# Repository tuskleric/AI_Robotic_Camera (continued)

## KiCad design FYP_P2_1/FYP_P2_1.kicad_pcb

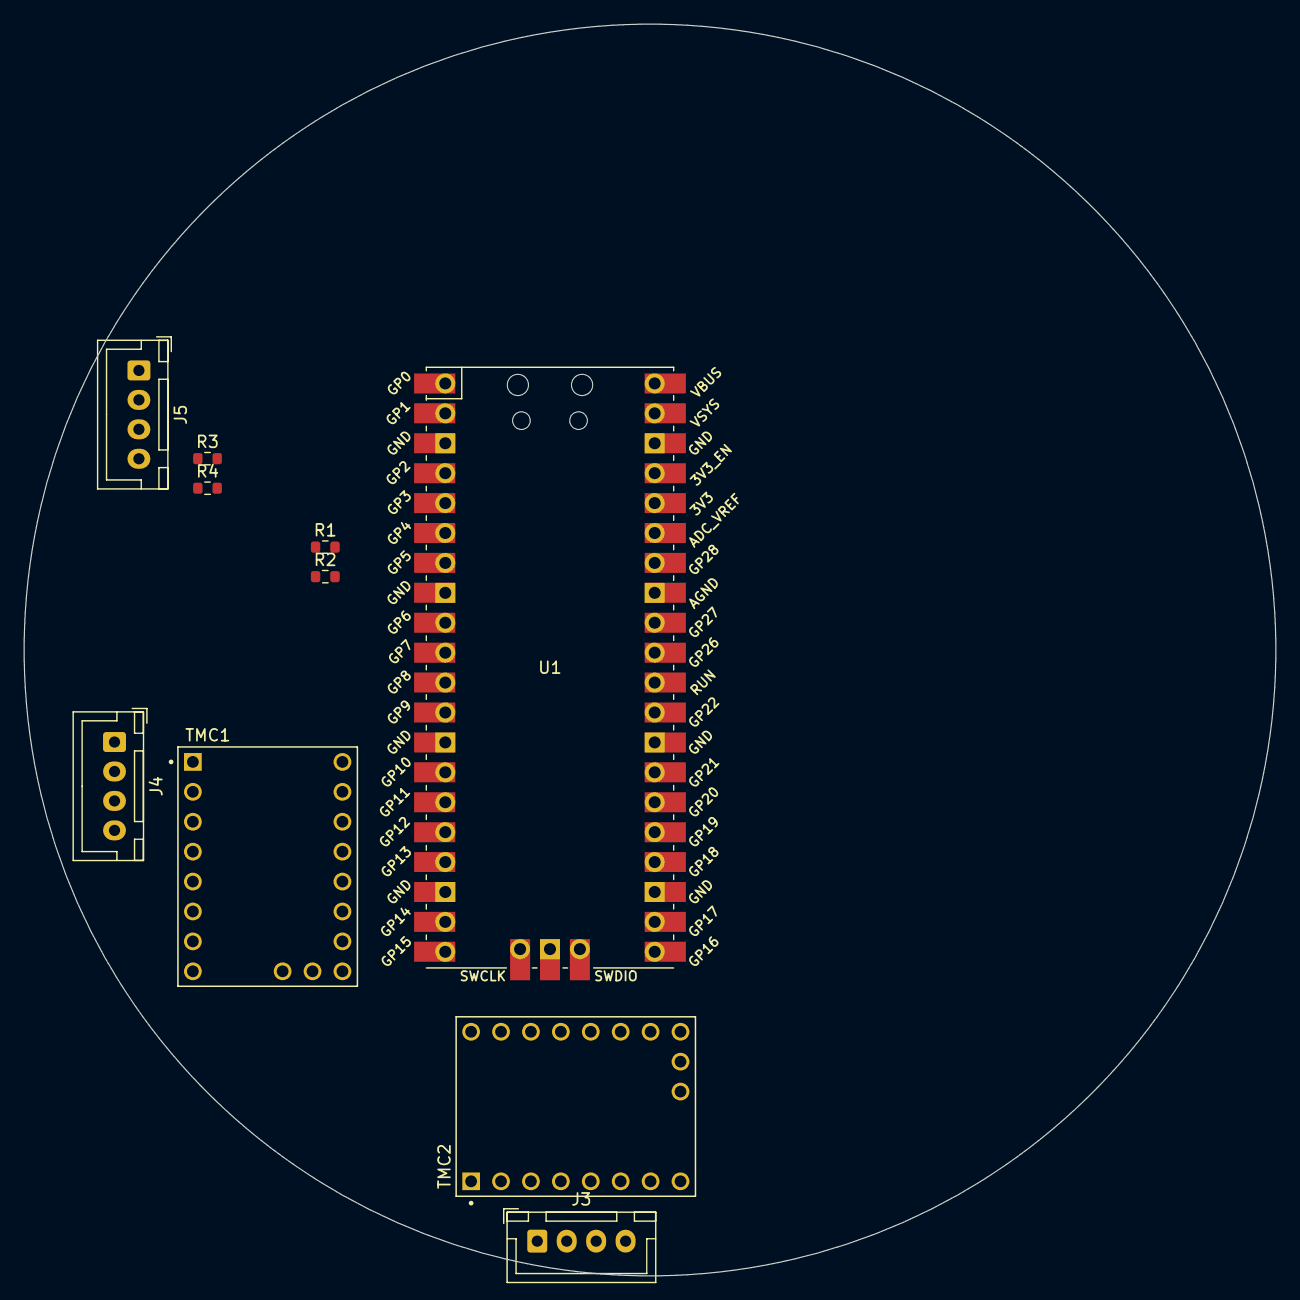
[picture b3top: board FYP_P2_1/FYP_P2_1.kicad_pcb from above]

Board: 4 copper layers, 106.3 x 106.3 mm, 10 parts (0 on the bottom side), 27 nets, no tracks yet.

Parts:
J3, J4, J5: Conn_01x04; JST_XH_B4B-XH-A_1x04_P2.50mm_Vertical
R1, R2: TBD; R_0603_1608Metric
R3, R4: 4k7; R_0603_1608Metric
TMC1, TMC2: MODULE_TMC2209_SILENTSTEPSTICK
U1: Pico; RPi_Pico_SMD_TH

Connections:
+3V3: R1.2, R2.2, R3.2, R4.2
+12V: TMC1.2 (VDD), TMC2.2 (VDD)
/MotorA1A: J4.2, TMC1.4 (1A)
/MotorA1B: J4.1, TMC1.3 (1B)
/MotorA2A: J4.3, TMC1.5 (2A)
/MotorA2B: J4.4, TMC1.6 (2B)
/MotorB1A: J3.2, TMC2.4 (1A)
/MotorB1B: J3.1, TMC2.3 (1B)
/MotorB2A: J3.3, TMC2.5 (2A)
/MotorB2B: J3.4, TMC2.6 (2B)
DIRA: TMC1.8 (DIR), U1.14 (GPIO10)
DIRB: TMC2.8 (DIR), U1.24 (GPIO18)
ENCODER_1A: R1.1, U1.4 (GPIO2)
ENCODER_1B: R2.1, U1.5 (GPIO3)
GND: TMC1.1 (GND), TMC1.7 (GND), TMC2.1 (GND), TMC2.7 (GND), U1.3 (GND), U1.8 (GND), U1.13 (GND), U1.23 (GND), U1.28 (GND), U1.38 (GND), U1.42 (GND)
MS1A: TMC1.14 (MS1), U1.20 (GPIO15)
MS1B: TMC2.14 (MS1), U1.22 (GPIO17)
MS2A: TMC1.13 (MS2), U1.19 (GPIO14)
MS2B: TMC2.13 (MS2), U1.21 (GPIO16)
SCL: J5.4, R4.1, U1.2 (GPIO1)
SDA: J5.3, R3.1, U1.1 (GPIO0)
STEPA: TMC1.9 (STEP), U1.15 (GPIO11)
STEPB: TMC2.9 (STEP), U1.25 (GPIO19)
UART_RX_A: TMC1.12 (UART_RX), U1.17 (GPIO13)
UART_RX_B: TMC2.12 (UART_RX), U1.27 (GPIO21)
UART_TX_A: TMC1.11 (UART_TX), U1.16 (GPIO12)
UART_TX_B: TMC2.11 (UART_TX), U1.26 (GPIO20)

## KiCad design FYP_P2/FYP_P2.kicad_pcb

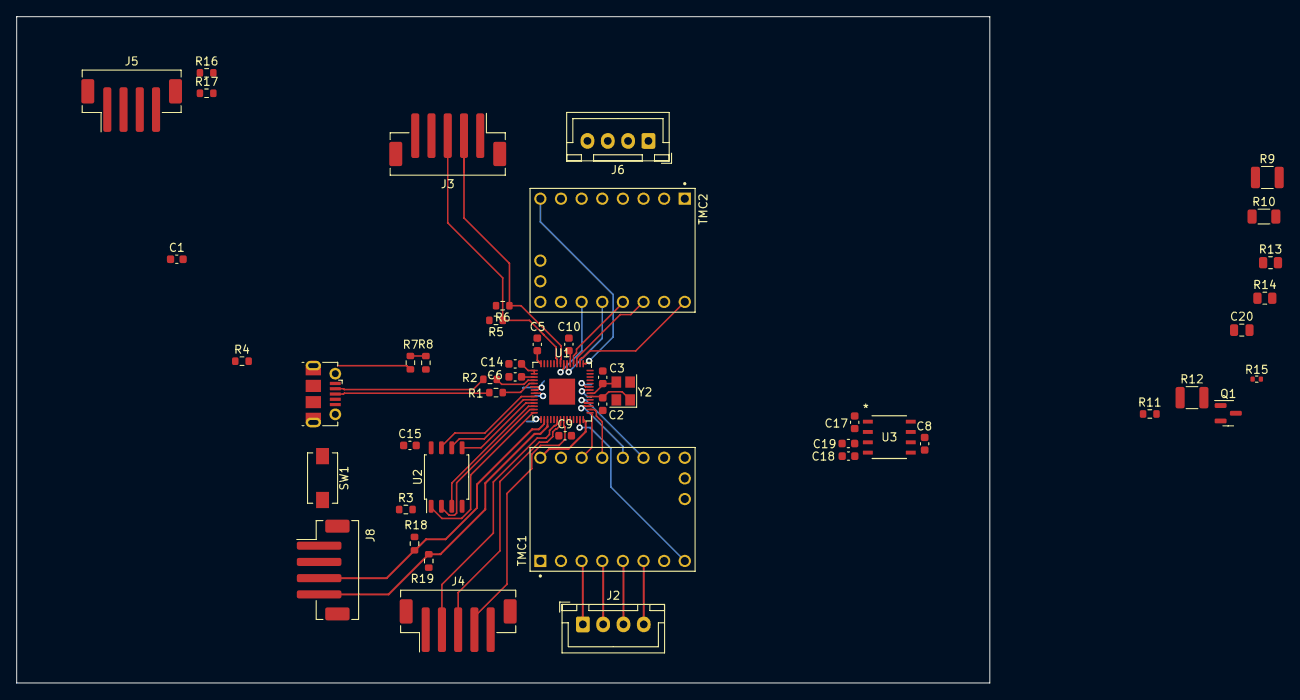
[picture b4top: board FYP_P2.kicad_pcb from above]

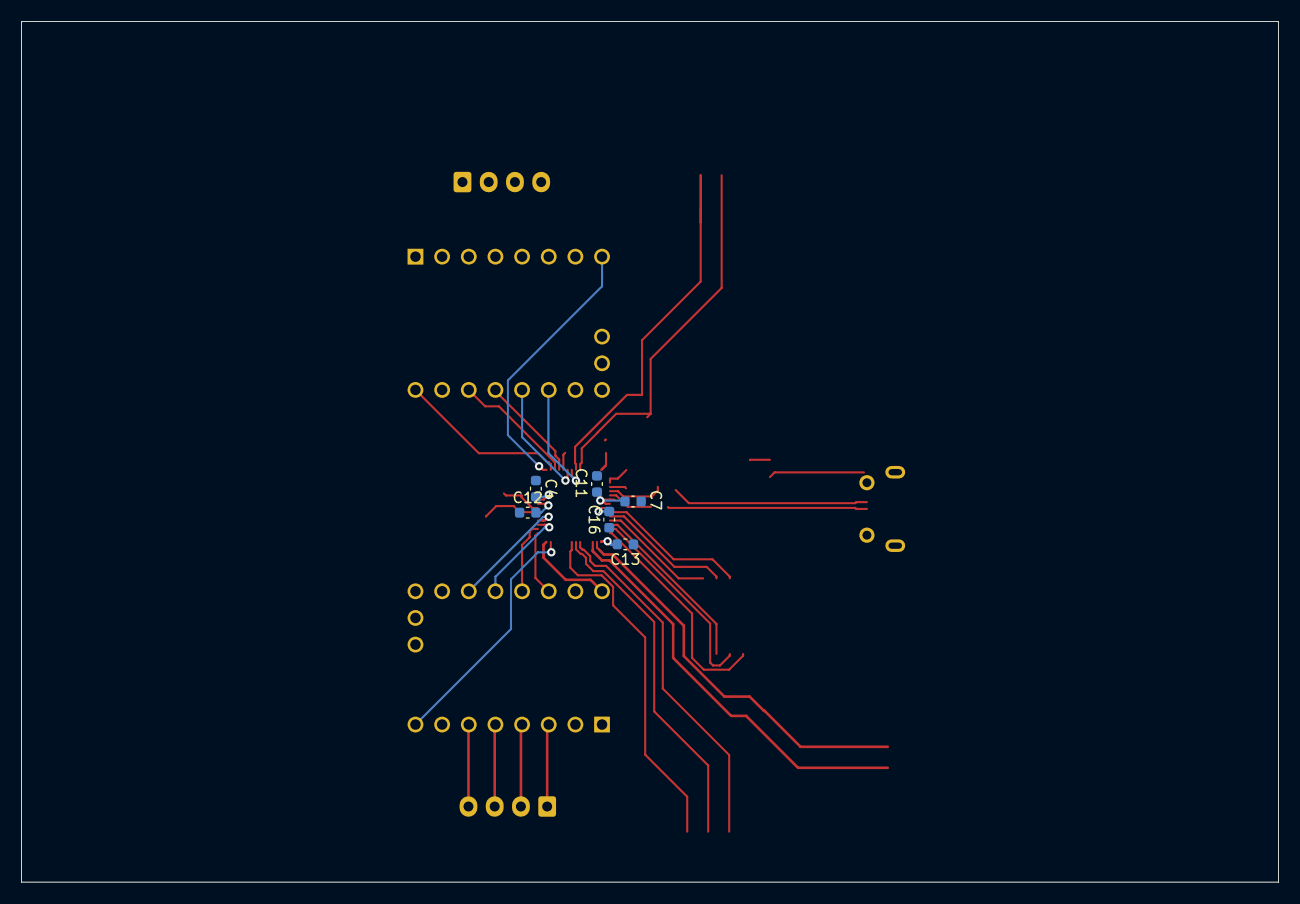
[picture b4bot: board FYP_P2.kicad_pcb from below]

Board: 4 copper layers, 119.8 x 82.0 mm, 54 parts (6 on the bottom side), 57 nets.

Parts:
C1: 4u7; C_0603_1608Metric
C2, C3: 15p; C_0603_1608Metric
C4, C5, C7, C9, C10, C11, C12, C13, C15, C16, C17: 100n; C_0603_1608Metric
C6, C14, C19: 1u; C_0603_1608Metric
C8: 10u; C_0603_1608Metric
C18: 22u; C_0603_1608Metric
C20: 22uF; C_0805_2012Metric
J1: USB_B_Micro; USB_Micro-B_Molex-105017-0001
J2, J6: Conn_01x04; JST_XH_B4B-XH-A_1x04_P2.50mm_Vertical
J3, J4: Conn_01x05; JST_PH_B5B-PH-SM4-TB_1x05-1MP_P2.00mm_Vertical
J5, J8: Conn_01x04; JST_PH_B4B-PH-SM4-TB_1x04-1MP_P2.00mm_Vertical
Q1: Q_PMOS_GSD; SOT-23
R1, R2: 27R; R_0603_1608Metric
R3: 1k; R_0603_1608Metric
R4: DNF; R_0603_1608Metric
R5, R6: TBD; R_0603_1608Metric
R7: 27k; R_0603_1608Metric
R8: 47k; R_0603_1608Metric
R9, R12: 2M; R_1210_3225Metric
R10: 560k; R_1206_3216Metric
R11: 33k; R_0603_1608Metric
R13: 150k; R_0805_2012Metric
R14: 22k; R_0805_2012Metric
R15: 100k; R_0402_1005Metric
R16, R17, R18, R19: 4k7; R_0603_1608Metric
SW1: SW_SPST; SW_SPST_EVQPE1
TMC1, TMC2: MODULE_TMC2209_SILENTSTEPSTICK
U1: RP2040; QFN-56-1EP_7x7mm_P0.4mm_EP3.2x3.2mm
U2: W25Q128JVS; SOIC-8_5.23x5.23mm_P1.27mm
U3: L6981N33DR; SO8L_L6981N33DR_STM-L
Y2: Crystal_GND24; Crystal_SMD_3225-4Pin_3.2x2.5mm

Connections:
+1V1: C4.2, C6.1, C16.2, U1.23 (DVDD), U1.45 (VREG_VOUT), U1.50 (DVDD)
+3V3: C5.2, C7.2, C9.2, C10.2, C11.2, C12.2, C13.2, C14.2, C15.1, C18.1, J4.1, J5.1, J8.1, R4.1, R5.2, R6.2, R16.2, R17.2, R18.2, R19.2, U1.1 (IOVDD), U1.10 (IOVDD), U1.22 (IOVDD), U1.33 (IOVDD), U1.42 (IOVDD), U1.43 (ADC_AVDD), U1.44 (VREG_IN), U1.48 (USB_VDD), U1.49 (IOVDD), U2.8 (VCC), U3.4 (FB/VOUT)
+12V: C8.2, C20.1, J3.1, Q1.2 (S), TMC1.2 (VDD), TMC2.2 (VDD), U3.5 (EN/CLKIN), U3.7 (VIN)
/MotorA1A: J2.2, TMC1.4 (1A)
/MotorA1B: J2.1, TMC1.3 (1B)
/MotorA2A: J2.3, TMC1.5 (2A)
/MotorA2B: J2.4, TMC1.6 (2B)
/MotorB1A: J6.2, TMC2.4 (1A)
/MotorB1B: J6.1, TMC2.3 (1B)
/MotorB2A: J6.3, TMC2.5 (2A)
/MotorB2B: J6.4, TMC2.6 (2B)
/PWR/+Batt: R9.1, R12.1
/QSPI_SCLK: U1.52 (QSPI_SCLK), U2.6 (CLK)
/QSPI_SD0: U1.53 (QSPI_SD0), U2.5 (DI(IO0))
/QSPI_SD1: U1.55 (QSPI_SD1), U2.2 (DO(IO1))
/QSPI_SD2: U1.54 (QSPI_SD2), U2.3 (IO2)
/QSPI_SD3: U1.51 (QSPI_SD3), U2.7 (IO3)
/QSPI_SS: R3.1, R4.2, U1.56 (QSPI_SS), U2.1 (~CS)
/USB_DETECT: R7.1, R8.2, U1.12 (GPIO9)
/USB_N: J1.2 (D-), R2.1
/USB_P: J1.3 (D+), R1.1
/~USB_BOOT: R3.2, SW1.2 (B)
BATT_SENSE_HV: R12.2, R13.1, U1.38 (GPIO26_ADC0)
BATT_SENSE_LV: R9.2, R10.1, U1.39 (GPIO27_ADC1)
DIRA: TMC1.8 (DIR), U1.13 (GPIO10)
DIRB: TMC2.8 (DIR), U1.29 (GPIO18)
ENCODER_1A: J3.2, R6.1, U1.36 (GPIO24)
ENCODER_1B: J3.3, R5.1, U1.37 (GPIO25)
ENCODER_2A: J4.2, U1.6 (GPIO4)
ENCODER_2B: J4.3, U1.7 (GPIO5)
ENCODER_2C: J4.4, U1.8 (GPIO6)
GND: C1.2, C2.1, C3.1, C4.1, C5.1, C6.2, C7.1, C8.1, C9.1, C10.1, C11.1, C12.1, C13.1, C14.1, C15.2, C16.1, C18.2, C19.2, C20.2, J1.5 (GND), J1.6 (Shield), J3.5, J4.5, J5.2, J8.2, R8.1, R11.2, R14.2, R15.2, SW1.1 (A), TMC1.1 (GND), TMC1.7 (GND), TMC2.1 (GND), TMC2.7 (GND), U2.4 (GND), U3.6 (AGND), U3.8 (PGND), Y2.2, Y2.4
MS1A: TMC1.14 (MS1), U1.18 (GPIO15)
MS1B: TMC2.14 (MS1), U1.35 (GPIO23)
MS2A: TMC1.13 (MS2), U1.17 (GPIO14)
MS2B: TMC2.13 (MS2), U1.34 (GPIO22)
unnamed: Q1.1 (G), R15.1
unnamed: R10.2, R11.1
unnamed: R13.2, R14.1
unnamed: R2.2, U1.46 (USB_DM)
unnamed: R1.2, U1.47 (USB_DP)
unnamed: C2.2, U1.20 (XIN), Y2.1
unnamed: C3.2, U1.21 (XOUT), Y2.3
unnamed: C17.2, U3.2 (BOOT)
unnamed: C17.1, U3.1 (SW)
unnamed: C19.1, U3.3 (VCC)
SCL: J8.4, R19.1, U1.3 (GPIO1)
SCL_PI: J5.4, R17.1, U1.5 (GPIO3)
SDA: J8.3, R18.1, U1.2 (GPIO0)
SDA_PI: J5.3, R16.1, U1.4 (GPIO2)
STEPA: TMC1.9 (STEP), U1.14 (GPIO11)
STEPB: TMC2.9 (STEP), U1.30 (GPIO19)
UART_RX_A: TMC1.12 (UART_RX), U1.16 (GPIO13)
UART_RX_B: TMC2.12 (UART_RX), U1.32 (GPIO21)
UART_TX_A: TMC1.11 (UART_TX), U1.15 (GPIO12)
UART_TX_B: TMC2.11 (UART_TX), U1.31 (GPIO20)
VBUS: C1.1, J1.1 (VBUS), R7.2

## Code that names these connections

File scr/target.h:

#ifndef TARGET_H
#define TARGET_H


//motors

//motor X
#define STEP_X   6
#define DIR_X    7
#define EN_A     28
#define MS1A 27
#define MS1B 26

//motor Y
#define STEP_Y   19
#define DIR_Y   18

#define EN_B 22
#define MS2A 21
#define MS2B 20
#define ENABLE_12_V 15



#define SLEEP_PIN  17 //any GPIO pin

//led on PICO
#define LED_PIN 25

//encoders
    //tilt
#define ENCODER_A  12
#define ENCODER_B  13

    //pan




#endif

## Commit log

2024-03-20 deleted redundent file
2024-03-21 RPM to FREQ function
2024-03-21 test commit
2024-04-01 working code for spinning turntable. need to work out CMAKE for sleep library
2024-04-02 Getting vscode working
2024-04-02 More changes
2024-04-02 Please just commit
2024-04-02 merging fixes
2024-04-02 Fixing issue with vscode
2024-04-26 Added on/off mode for stepper motor and state machine counter mode
2024-04-26 prototype 1, test 2 code
2024-05-10 Build folder should now be ignored
2024-05-10 tidying up
2024-05-13 added PCB
2024-05-16 Made development on I2C communication with raspberry pi
2024-05-24 UART mostly working w tmc2209. need to tune coolstep
2024-05-25 Encoder functionality
2024-05-26 scheduler is working now. just need to add tasks
2024-05-26 clean up
2024-05-30 Revert "clean up"
    This reverts commit 1a99e20e6b789471d7948f290d0e3b8959e412e1.
2024-05-30 Revert "scheduler is working now. just need to add tasks"
    This reverts commit d82a4bdf3cde3ae16663e940aa4d823298b14c0a.
2024-05-30 fixing mistakes
2024-06-24 scheduler implemented for two motor movement. still fixing UART comms
2024-07-08 Initial dbus functions working
2024-07-08 Pi now recieves from dbus and transmits to raspberry pi
2024-07-18 Initial attempt at closed loop control - Not Working
2024-07-19 updated scheduler
2024-07-19 Added individual two motor functions
2024-07-19 Implimenting more sophisticated motor control
2024-07-23 Fixed error with motors not rotating far enough
2024-07-23 Basic one int i2c set up
2024-07-23 Expanded control for both axes and fixed jitter when target is reached
2024-07-25 starting refactoring main
2024-08-06 Finally reading from thermal recorder
2024-08-07 Cleaned up go formatting and naming
2024-08-07 Created constants and made a function for converting pixels coords to target angles
2024-08-07 Integrated some data processing and improved modularity
2024-08-07 angles are now converted to bytes and transmitted via i2c
2024-08-07 FOVs now correctly reflect data sheet
2024-08-09 Fixed up i2c comms for both pico and pi
2024-08-11 12Volt power is now enabled
2024-08-22 new target file for the new PCB
2024-08-22 testing changes made to these file. while(1) loops used to debug uart
2024-08-23 started on FSM
2024-08-23 Added update_state function and logic
2024-08-23 Added getState
2024-09-19 working code
2024-10-08 Added in the imu and rf source files. This is the final code that ended up on the final design but I forgot to push.
2024-10-09 PCB files added
